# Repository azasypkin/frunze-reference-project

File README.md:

# Frunze Reference Project
Dead Simple C++ AVR timer based based on ATTiny 85 MCU.

Project template is generated with the following command:

```
platformio init --ide clion --board attiny85
```

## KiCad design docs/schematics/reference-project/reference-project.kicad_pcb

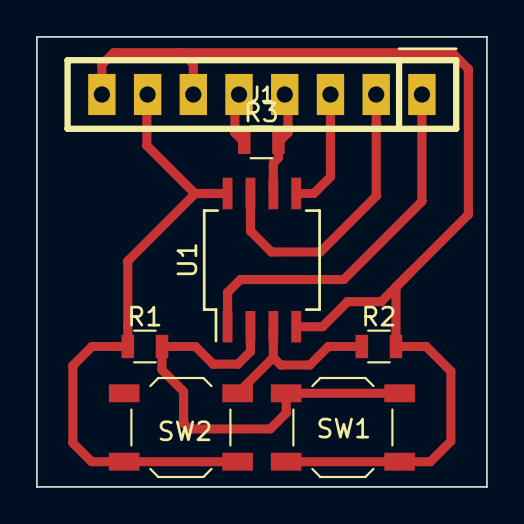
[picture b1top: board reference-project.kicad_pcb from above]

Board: 2 copper layers, 25.0 x 25.0 mm, 7 parts (0 on the bottom side), 9 nets.

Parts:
J1: Conn_01x08_Female; CONN-100MIL-F-1x8
R1, R2: 10K; R_0805
R3: 220; R_0805
SW1: RESET; SW_SPST_TL3342
SW2: INPUT_5; SW_SPST_TL3342
U1: ATTINY85-20SU; SO-8_5.3x6.2mm_Pitch1.27mm

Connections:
GND: J1.6, J1.8, R2.2, SW1.1, U1.4
unnamed: R1.2, SW1.2, U1.2
unnamed: R2.1, SW2.1, U1.3
PIN_1: J1.1, U1.1
PIN_5: J1.3, U1.5
PIN_6: J1.4, R3.2, U1.6
PIN_7: J1.2, U1.7
SPKR+: J1.5, R3.1
VCC: J1.7, R1.1, SW2.2, U1.8

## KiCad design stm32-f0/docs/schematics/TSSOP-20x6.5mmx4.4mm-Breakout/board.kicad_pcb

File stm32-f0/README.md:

# Frunze Reference Project

Project template is generated with the following command:

```
platformio init --ide clion --board disco_f051r8
```

Framework should be set to [cmsis](http://docs.platformio.org/en/latest/frameworks/cmsis.html).

## Custom platform

Currently `platformio` does not support `cmsis` framework for `stm32f0` MCUs, so we should point to
the [forked and patched platform instead](https://github.com/azasypkin/platform-ststm32/releases/tag/v4.1.1).

The patched `platform-ststm32` requires the following changes in `platformio.ini`:

* `platform = https://github.com/azasypkin/platform-ststm32.git#stm32f0-cmsis` - to point to the patched platform;
* `build_unflags = -nostdlib -nostartfiles` - required for the `__libc_init_array` to work with `Platformio`

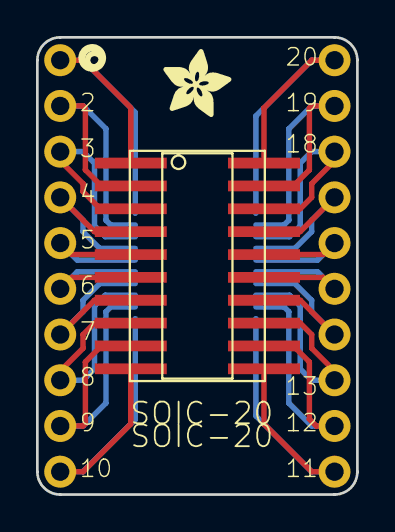
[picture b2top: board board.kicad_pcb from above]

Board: 2 copper layers, 17.8 x 25.4 mm, 6 parts (0 on the bottom side), 20 nets.

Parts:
U$1: 20-PINSOIC-NW; SO20-NW
U$2: 20-PINTSSOP-NW; TSSOP20-NW
U$3, U$4: PADS-10
U$5, U$6: ADAFRUIT_3.5MM

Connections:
unnamed: U$1.P$1, U$2.P$20, U$3.1
unnamed: U$1.P$2, U$2.P$19, U$3.2
unnamed: U$1.P$3, U$2.P$18, U$3.3
unnamed: U$1.P$4, U$2.P$17, U$3.4
unnamed: U$1.P$5, U$2.P$16, U$3.5
unnamed: U$1.P$6, U$2.P$15, U$3.6
unnamed: U$1.P$7, U$2.P$14, U$3.7
unnamed: U$1.P$8, U$2.P$13, U$3.8
unnamed: U$1.P$9, U$2.P$12, U$3.9
unnamed: U$1.P$10, U$2.P$11, U$3.10
unnamed: U$1.P$20, U$2.P$1, U$4.1
unnamed: U$1.P$19, U$2.P$2, U$4.2
unnamed: U$1.P$18, U$2.P$3, U$4.3
unnamed: U$1.P$17, U$2.P$4, U$4.4
unnamed: U$1.P$16, U$2.P$5, U$4.5
unnamed: U$1.P$15, U$2.P$6, U$4.6
unnamed: U$1.P$14, U$2.P$7, U$4.7
unnamed: U$1.P$13, U$2.P$8, U$4.8
unnamed: U$1.P$12, U$2.P$9, U$4.9
unnamed: U$1.P$11, U$2.P$10, U$4.10

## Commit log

2017-08-27 Initial commit.
2017-08-27 Add UART output support.
2017-08-27 Increase upload speed and switch to `qio` flashing mode.
2017-08-28 Include some documentation for esp-12f.
2017-08-28 Migrate to custom `nonos-sdk` platformion framework that is based on SDK 2.1.0.
2017-11-04 Updated to v2.
2017-11-04 Updated to v3.
2017-11-04 Add PISO for 165 Shift Register.
2017-11-04 New version of schematics.
2017-11-04 Better integration of set/reset button with sleep mode.
2017-11-04 Process reset interruption
2017-11-04 Finished schematics.
2017-11-04 Initial version of schematics.
2017-11-04 Full SMD version.
2017-11-04 Dump shift register content only on the long Reset button press.
2017-11-04 Prepared Gerber files.
2017-11-04 Include speaker lib.
2018-01-23 Update KiCad schematics. Upgrade Platformio to 3.5.x.
2018-03-24 Restructure reference projects to accomodate different platforms in one repository.
2018-03-24 Add blinky for stm32f051x8.
2018-03-25 [stm32-f0] Adapt code to work with stm32f042 and stm32f051.
2018-03-25 [stm32-f0] Add specs and other docs.
2018-03-28 Initial schematic and gerber files for tssop-20 adapter.
2018-03-31 Update TSSOP-20 breakout board G-Code. Describe SWD programming of STM32F042 with STM32F0Discovery board.
2018-04-01 Initial commit of stm32-f0-rust.
2018-04-01 Add stm32f0x1 crate generated with `svd2rust` for `stm32f0x1` MCUs.
2018-04-01 Include kicad project file for `avr-attiny85`.
2018-04-01 Implement Rust Blinky for `STM32F0Discovery`
2018-04-01 Add stm32f0x2 crate generated with `svd2rust` for `stm32f0x2` MCUs.
2018-04-01 Add blinky example for `stm32f042`.
2018-04-02 Add example with GPIO interrupt in C.
2018-04-03 [stm32f0-rust] Add support for external interrupts.
2018-04-03 [stm32f0-rust] Add more inline docs.
2018-04-04 [stm32f0] Add Sleep mode example.
2018-04-06 [stm32-f0-rust] Update dependencies.
2018-04-06 [stm32-f0] Initial PWM audio implementation.
2018-04-07 [stm32-f0-rust] Initial version of rust pwm based audio (does not work yet).
2018-04-07 [stm32-f0-rust] Fix rust pwm audio example.
2018-04-08 Reorganize delay routines.
2018-04-08 Update to the latest nightly and cortex-m-rt crate.
2018-04-08 Get rid of Xargo completely.
2018-04-09 Migrate to `cortex-m-rt = "0.4.0"`.
2018-04-10 Update codebase to be in line with the latest crates.
2018-04-11 Reformat stm32f0x1 lib source file.
2018-04-15 Initial implementation of RTC wrappper.
2018-04-15 Use `Time` to configure time and alarm.
2018-04-15 Reschedule alarm every 5s.
2018-04-17 Reformat stm32f0x1 crate with `form`.
2018-04-18 Use beeper, alarm and standby mode together.
2018-04-18 Make `Beeper.configure` --> `Beeper::configure`.
2018-04-18 Split `stm32f0x2` into modules.
2018-04-19 Intermediate step to stm32f042x6 (RTC alarm does not work).
2018-04-21 Fix linker files (memory.x was always used for some reason).
2018-04-24 Use `openocd.cfg`. Enable `s` optimization of `--release`.
2018-04-24 Initial implementation of button wakeup.
2018-04-25 Simplify borrowing of peripherals.
2018-04-25 Improve API ergonomics.
2018-04-25 Distinguish short, long and very long button presses.
2018-04-26 Update dependencies.
2018-04-26 First mode dependent alarm/setup.
2018-04-26 Do not schedule alarm on short press.
2018-04-27 Fix clippy warnings (and disable them for stm32f0xx crates.
2018-04-27 Customize alarm with button.
2018-04-28 Allow set alarm in 3 different presets.
2018-04-28 Use different melodies for setup and reset actions.
2018-04-30 Make final project work on stm32f042
2018-05-01 Initial schematics for the stm32 block.
2018-05-01 [PCB][STM32-Block] Use correct footprints for the pin sockets.
2018-05-01 [PCB][STM32-Block] Use single 7-pin socket instead of two.
2018-05-01 [PCB][STM32-Block] Reduce PCB edges.
2018-05-01 [PCB][STM32-Block] Export block 3D model.
2018-05-01 [PCB][STM32-Block] Update traces screenshot.
2018-05-06 Update device crates to compile with the latest nightly
2018-05-06 Update `cc` dependency.
2018-05-13 Regenerate stm32f0x1 and stm32f0x2 crates with the latest svd2rust.
2018-05-14 Update `cortex-m-rt` to `0.5.1` to avoid issues with too frequent re-compilation.
2018-05-19 Update `cortex-m` to `0.5.2`.
2018-05-19 Use dedicated API for managing `DEEPSLEEP` bit.
2018-05-21 Add stm32 block manufacturing files.
2018-05-21 Add correct footprint for smt32 TSSOP-20.
2018-06-08 Add schematics for the `Bus` block.
2018-06-08 Add schematics for `CR2032` block.
2018-06-08 Update dependencies for `stm32f0x1` crate.
2018-06-08 Regenerate `stm32f0x1` crate with `svd2rust:0.13.1`.
2018-06-08 Update dependencies for `stm32f0x2`.
2018-06-08 Regenerate `stm32f0x2` crate with `svd2rust:0.13.1`.
2018-06-08 Update dependencies. Fix failures caused by latest Rust Nightly.
2018-06-15 Add `Button Block` schematics.
2018-08-05 Update dependencies in `stm32f0x1` and `stm32f0x2` crates.
2018-08-05 Update dependencies in the reference project.
2018-11-04 Update dependencies + re-generate proxies with the latest svd2rust.
2018-12-17 Remove tssop-20 breakout board from this project.
2018-12-17 Update Readme files.
2018-12-17 Update stm32f0x2 crate.
2018-12-17 Update stm32f0x1 crate.
2018-12-19 Update Readme with DFU firmware upload method. Upload DFU manual.
